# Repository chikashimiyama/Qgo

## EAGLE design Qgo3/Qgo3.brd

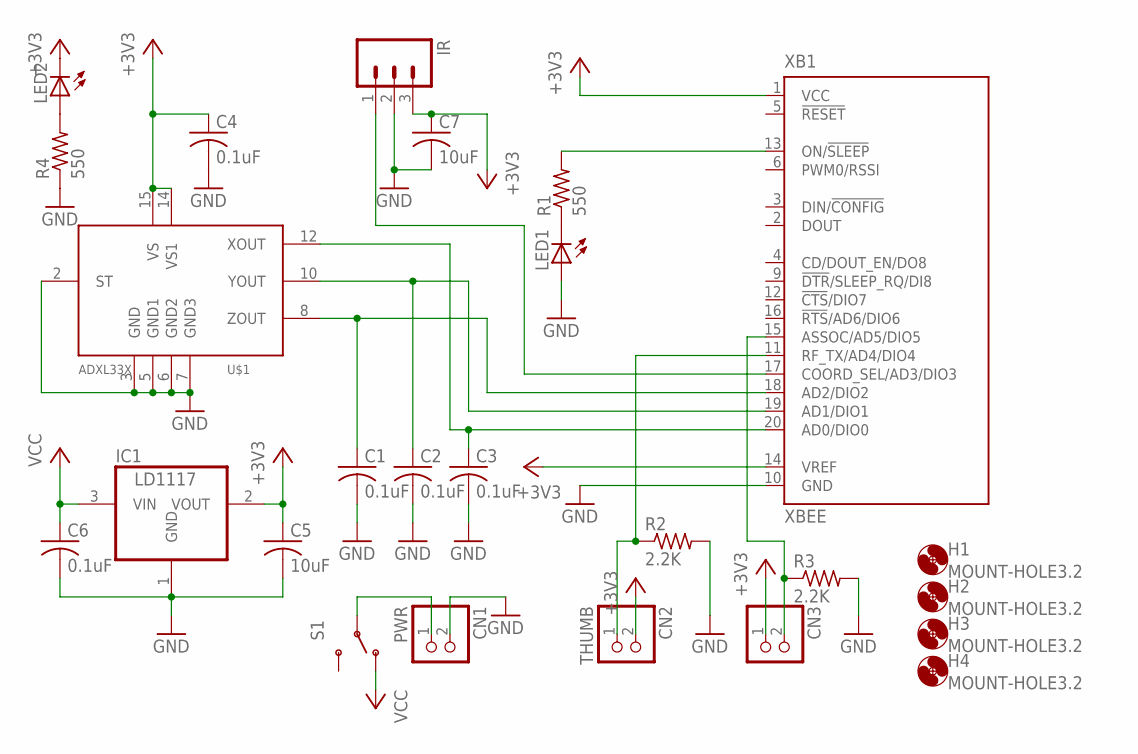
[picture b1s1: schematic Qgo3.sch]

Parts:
C1, C2, C3, C4, C6: 0.1uF; C1210
C5, C7: 10uF; C1210
CN1: PWR; JST-PH-2-THM-RA
CN2: THUMB; JST-PH-2-THM-RA
CN3: JST_2PIN-THM-RA; JST-PH-2-THM-RA
H1, H2, H3, H4: MOUNT-HOLE3.2; 3,2
IC1: LD1117; SOT223
IR: M03PTH; 1X03
LED1, LED2: LED5MM
R1, R4: 550; 0207/7
R2, R3: 2.2K; 0207/7
S1: SWITCH-SPDTPTH; SWITCH-SPDT
U$1: ADXL33X; 16LCSP
XB1: XBEE

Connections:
+3V3: C4.1, C5.1, C7.1, CN2.2 (1), CN3.1 (2), IC1.2 (VOUT), IR.3, LED2.K (C), U$1.14 (VS1), U$1.15 (VS), XB1.1 (VCC), XB1.14 (VREF)
GND: C1.2, C2.2, C3.2, C4.2, C5.2, C6.2, C7.2, CN1.2 (1), IC1.1 (GND), IR.2, LED1.A, R2.2, R3.2, R4.1, U$1.2 (ST), U$1.3 (GND), U$1.5 (GND1), U$1.6 (GND2), U$1.7 (GND3), XB1.10 (GND)
unnamed: C1.1, U$1.8 (ZOUT), XB1.18 (AD2/DIO2)
unnamed: C2.1, U$1.10 (YOUT), XB1.19 (AD1/DIO1)
unnamed: C3.1, U$1.12 (XOUT), XB1.20 (AD0/DIO0)
unnamed: IR.1, XB1.17 (COORD_SEL/AD3/DIO3)
unnamed: CN1.1 (2), S1.2
unnamed: LED1.K (C), R1.1
unnamed: R1.2, XB1.13 (ON/!SLEEP)
unnamed: CN2.1 (2), R2.1, XB1.11 (RF_TX/AD4/DIO4)
unnamed: LED2.A, R4.2
unnamed: CN3.2 (1), R3.1, XB1.15 (ASSOC/AD5/DIO5)
VCC: C6.1, IC1.3 (VIN), S1.1 (O)

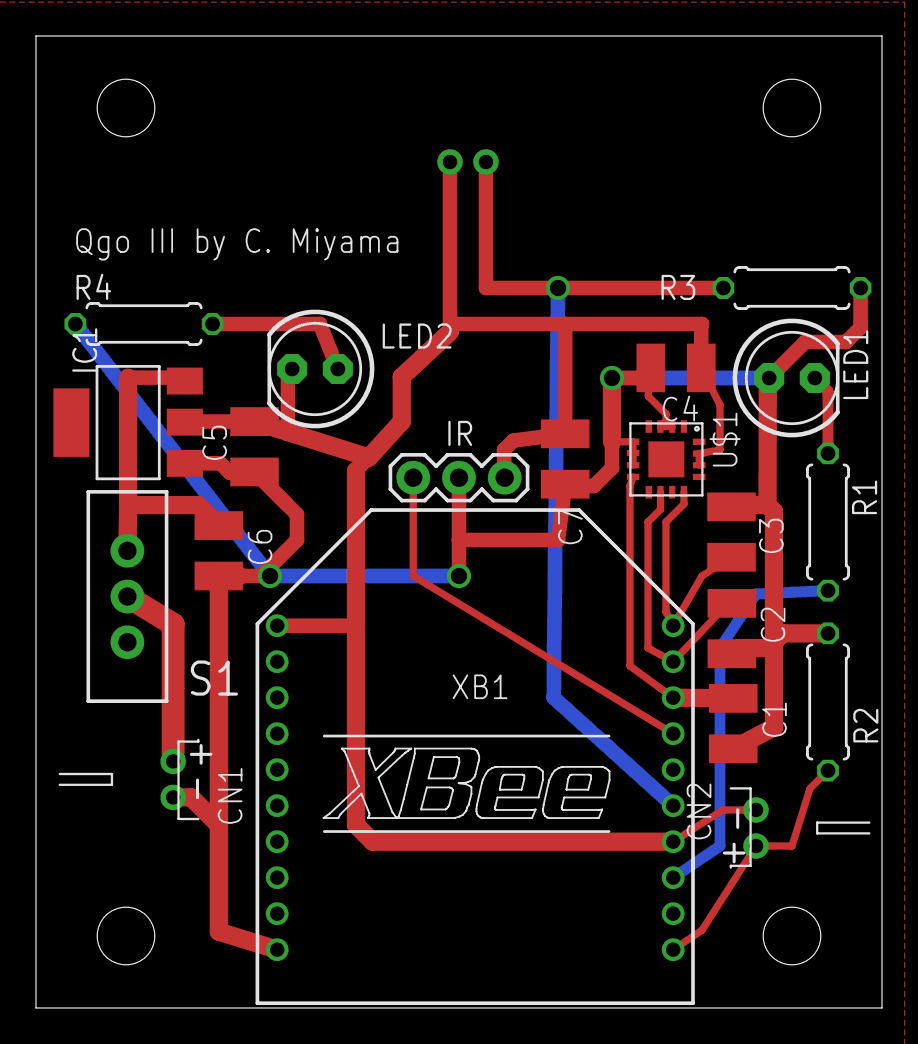
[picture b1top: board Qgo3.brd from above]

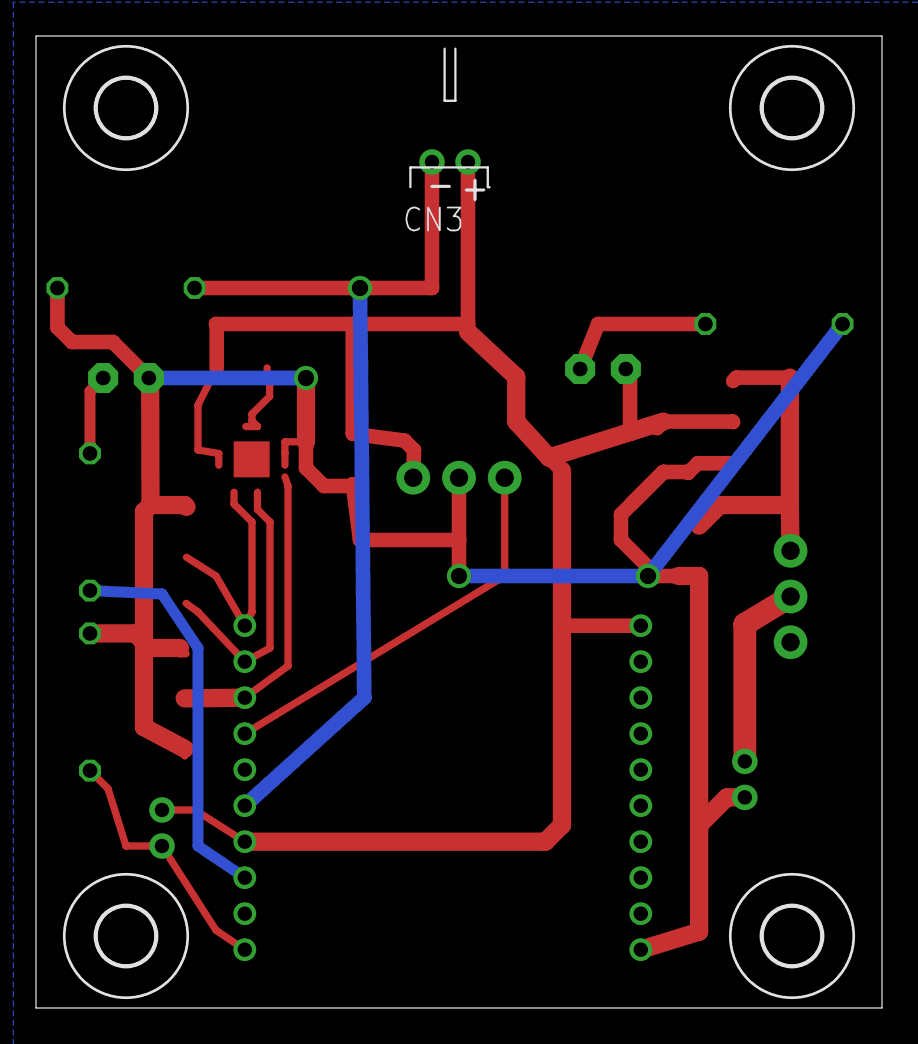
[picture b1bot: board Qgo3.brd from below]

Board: 2 copper layers, 47.0 x 54.0 mm, 25 parts (5 on the bottom side), 13 nets.

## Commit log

2014-05-24 initial

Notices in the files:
parts and their libraries:
SparkFun-Connectors: Licensing: Creative Commons ShareAlike 4.0 International - https://creativecommons.org/licenses/by-sa/4.0
